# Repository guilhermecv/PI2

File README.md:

# Projeto Integrador 2 - 2019/1

IFSC Engenharia Eletrônica

--> [Artigo LPAE](https://github.com/LPAE/pi2_eng_19_1/blob/master/Guilherme_Camargo_e_Jessica_Ribeiro/previa_artigo.md)

--> [Vídeo do projeto em funcionamento](https://www.youtube.com/watch?v=CO9-e8kDYCU)

Autores:

Guilherme Camargo Valese

Jéssica Ramos Ribeiro

## Hardware Utilizado

* Raspberry Pi 2B
* TCS 230
* MLX 90615
* JSN - SR04
* TCRT 5000
* LV1000 - CCD scanner
* LCD 16x2

## Instalação

O projeto utiliza a biblioteca wiringPi, incluída por  padrão nas versões do Raspbian

```bash
$ git clone https://github.com/guilhermecv/PI2.git
$ cd PI2/Raspberry/firmware
$ make
$ ./PI2
```

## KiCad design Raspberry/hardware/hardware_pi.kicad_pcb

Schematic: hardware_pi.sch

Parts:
BZ1: Buzzer; Buzzer_12x9.5RM7.6
C1: 100nF; C_0805_2012Metric_Pad1.29x1.40mm_HandSolder
D1: ON!; LED_0805_2012Metric_Pad1.12x1.40mm_HandSolder
D2: STATUS; LED_0805_2012Metric_Pad1.12x1.40mm_HandSolder
D3: IR_0; LED_0805_2012Metric_Pad1.12x1.40mm_HandSolder
D4: IR_1; LED_0805_2012Metric_Pad1.12x1.40mm_HandSolder
D5: IR_2; LED_0805_2012Metric_Pad1.12x1.40mm_HandSolder
D6: IR_4; LED_0805_2012Metric_Pad1.12x1.40mm_HandSolder
J101: raspberry; PinSocket_2x13_P2.54mm_Vertical
J201: LVL_HI; PinSocket_1x06_P2.54mm_Vertical
J202: LVL_LO; PinSocket_1x06_P2.54mm_Vertical
J203: DISPLAY; PinHeader_1x04_P2.54mm_Vertical
J204: TCS; PinHeader_1x05_P2.54mm_Vertical
J205: MLX; PinHeader_1x04_P2.54mm_Vertical
J401, J402, J403, J404: Conn_01x04; PinHeader_1x04_P2.54mm_Vertical
R1, R2: R_US; R_0805_2012Metric_Pad1.29x1.40mm_HandSolder
R3, R4, R5, R6, R401, R402, R403, R404, R501, R502, R503, R504, R505, R506, R507, R508, R601: R_Small; R_0805_2012Metric_Pad1.29x1.40mm_HandSolder
TP101, TP102: Test_Point; TestPoint_Pad_D1.5mm
U1: LM324A; SOIC-14_3.9x8.7mm_P1.27mm

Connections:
+3V3: C1.2, J101.1, J101.17, J202.3, J205.4, J401.2, J402.2, J403.2, J404.2, R1.1, R401.1, R402.1, R403.1, R404.1, R501.2, R503.2, R505.2, R507.2, U1.4 (V+)
+5V: J101.2, J101.4, J201.3, J203.3, J204.1
/BUZZER: J101.7, R601.2
/ECHO: J101.24
/IR_0: J101.18, R3.1, U1.1
/IR_1: J101.16, R4.1, U1.7
/IR_2: J101.12, R5.1, U1.8
/IR_3: J101.10, R6.1, U1.14
/LED_STATUS: J101.11, R2.1
/SCL_3V3: J101.5, J202.2, J205.2, TP102.1
/SCL_5V: J201.2, J203.1
/SDA_3V3: J101.3, J202.1, J205.1, TP101.1
/SDA_5V: J201.1, J203.2
/TCS_OUT: J101.23, J202.6
/TCS_S2: J101.21, J204.4
/TCS_S3: J101.19, J204.3
/TRIGGER: J101.26
GND: BZ1.2, C1.1, D1.1, D2.1, D3.1, D4.1, D5.1, D6.1, J101.6, J101.9, J101.14, J101.20, J101.25, J201.4, J202.4, J203.4, J204.2, J205.3, J401.3, J402.3, J403.3, J404.3, R502.2, R504.2, R506.2, R508.2, U1.11 (V-)
unnamed: BZ1.1, R601.1
unnamed: D1.2, R1.2
unnamed: D2.2, R2.2
unnamed: D3.2, R3.2
unnamed: D4.2, R4.2
unnamed: D5.2, R5.2
unnamed: D6.2, R6.2
unnamed: J201.6, J204.5
unnamed: J401.1, U1.3 (+)
unnamed: J401.4, R401.2
unnamed: J402.1, U1.5 (+)
unnamed: J402.4, R402.2
unnamed: J403.1, U1.10 (+)
unnamed: J403.4, R403.2
unnamed: J404.1, U1.12 (+)
unnamed: J404.4, R404.2
unnamed: R501.1, R502.1, U1.2 (-)
unnamed: R503.1, R504.1, U1.6 (-)
unnamed: R505.1, R506.1, U1.9 (-)
unnamed: R507.1, R508.1, U1.13 (-)

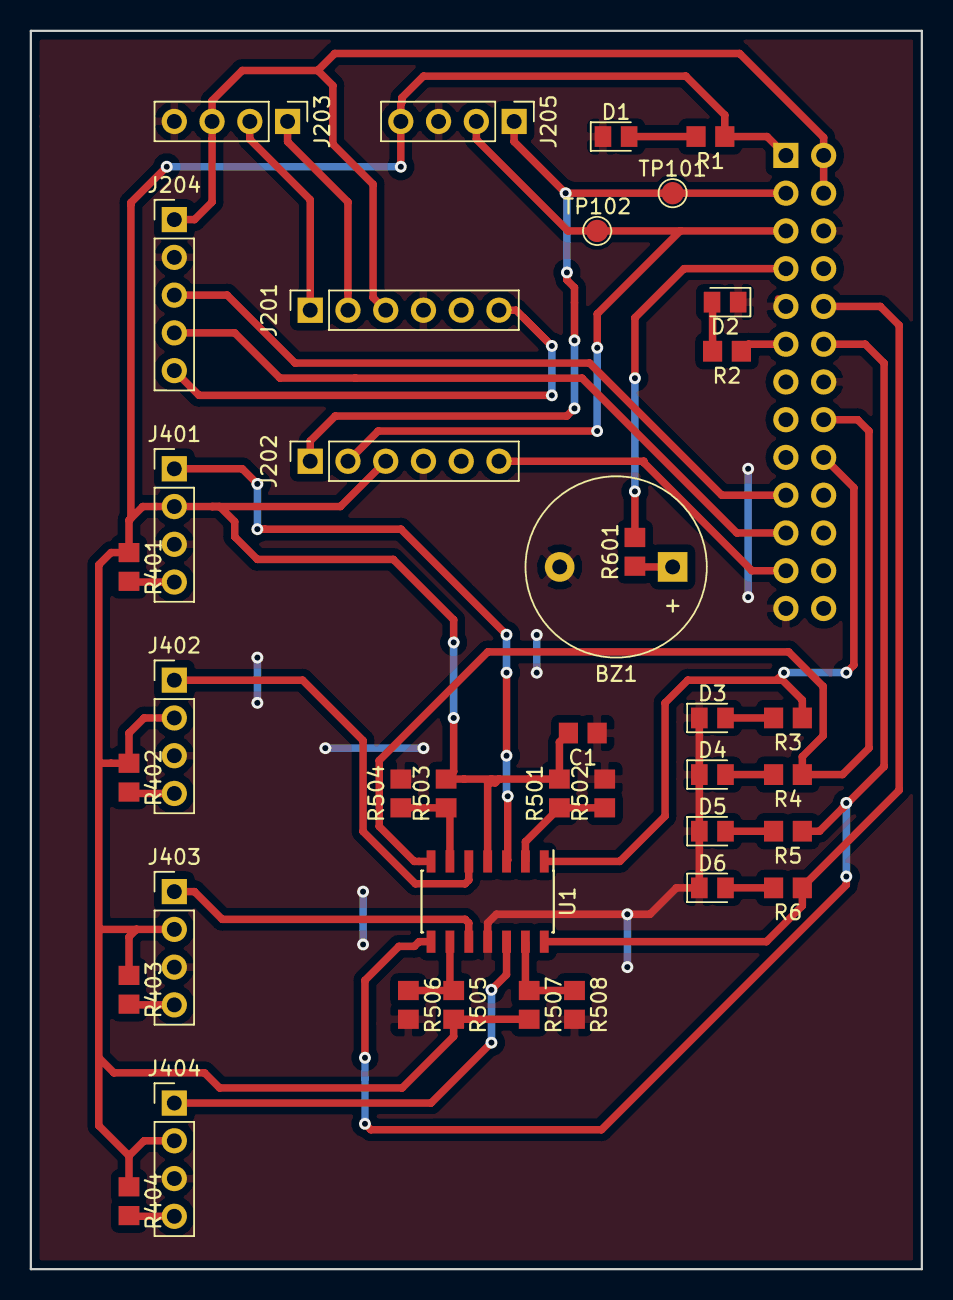
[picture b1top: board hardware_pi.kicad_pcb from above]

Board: 2 copper layers, 59.9 x 83.3 mm, 40 parts (1 on the bottom side), 36 nets.

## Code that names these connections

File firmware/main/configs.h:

/*
 * PI 2 - 2019/1
 * Configurações gerais do sistema
 */

//========== ATIVAÇÃO DOS MÓDULOS ============
#define USART_ON
//#define ULTRASSONIC_ON
//#define COLOR_ON
//#define TEMPERATURE_ON
//#define DISPLAY_ON
//#define OCR_ON        // FALTA IMPLEMENTAR ESTE MÓDULO
//#define WATCHDOG_ON   // AVALIAR NECESSIDADE DO WATCHDOG

//=========== MODOS DE OPERAÇÃO ==============
//#define TEST_MODE
//#define DEBUG_ON

//============= DEFINIÇÕES ===================
#define USART_BAUD      9600
#define LCD_ADDR        0x27
//#define MLX_ADDR

//=== CONFIGURAÇÕES DO SENSOR ULTRASSONICO ===
#define TRIGGER_PIN     9
#define ECHO_PIN        8
#define OFFSET          0     // Talvez passar isso para uma função

//===== CONFIGURAÇÕES DO SENSOR DE COR =======
#define TCS_S0          2
#define TCS_S1          3
#define TCS_S2          4
#define TCS_S3          5
#define TCS_OUT         6

//=== CONFIGURAÇÕES DOS SENSORES DE POSIÇÃO ==
#define IR_0            A0
#define IR_1            A1
#define IR_2            A2
#define IR_3            A3

#define menu_button     7
#define BUZZER_PIN      12

//================================================
//==== CONFIGURAÇÕES DE LIMITES DE PARÂMETROS ====
//================================================





/* controles do sistema, não é necessário alterar estas opções*/
#ifdef DEBUG_ON
#ifndef USART_ON
#define USART_ON
#endif
#define debug_msg(c)    c
#else
#define debug_msg(c)
#endif

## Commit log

2019-03-27 creating readme.md
2019-04-04 testing
2019-04-04 adding files
2019-04-17 fluxograma
2019-04-17 previa artigo
2019-04-24 update!
2019-05-25 update repository
2019-05-26 Leituras incorretas do TCS/ Backlight não funciona
2019-05-28 not tested
2019-06-26 funçoes basicas funcionando :)
2019-06-26 Sensor de temperatura funcionando :)
2019-07-01 versao para teste
2019-07-02 teste OCR
2019-07-05 versao com OCR
2019-07-07 codigo de barras funcionando
2019-07-08 versao final
2019-09-09 adicionado novos arquivos
2019-09-13 adicionado link para vídeo do projeto
2019-09-13 display adicionado
2019-10-16 arquivos adicionados
2019-10-21 wdt not working
2019-10-22 SNCT2019
2019-10-23 teste SNCT
2019-10-23 alteracoes funcionamento
